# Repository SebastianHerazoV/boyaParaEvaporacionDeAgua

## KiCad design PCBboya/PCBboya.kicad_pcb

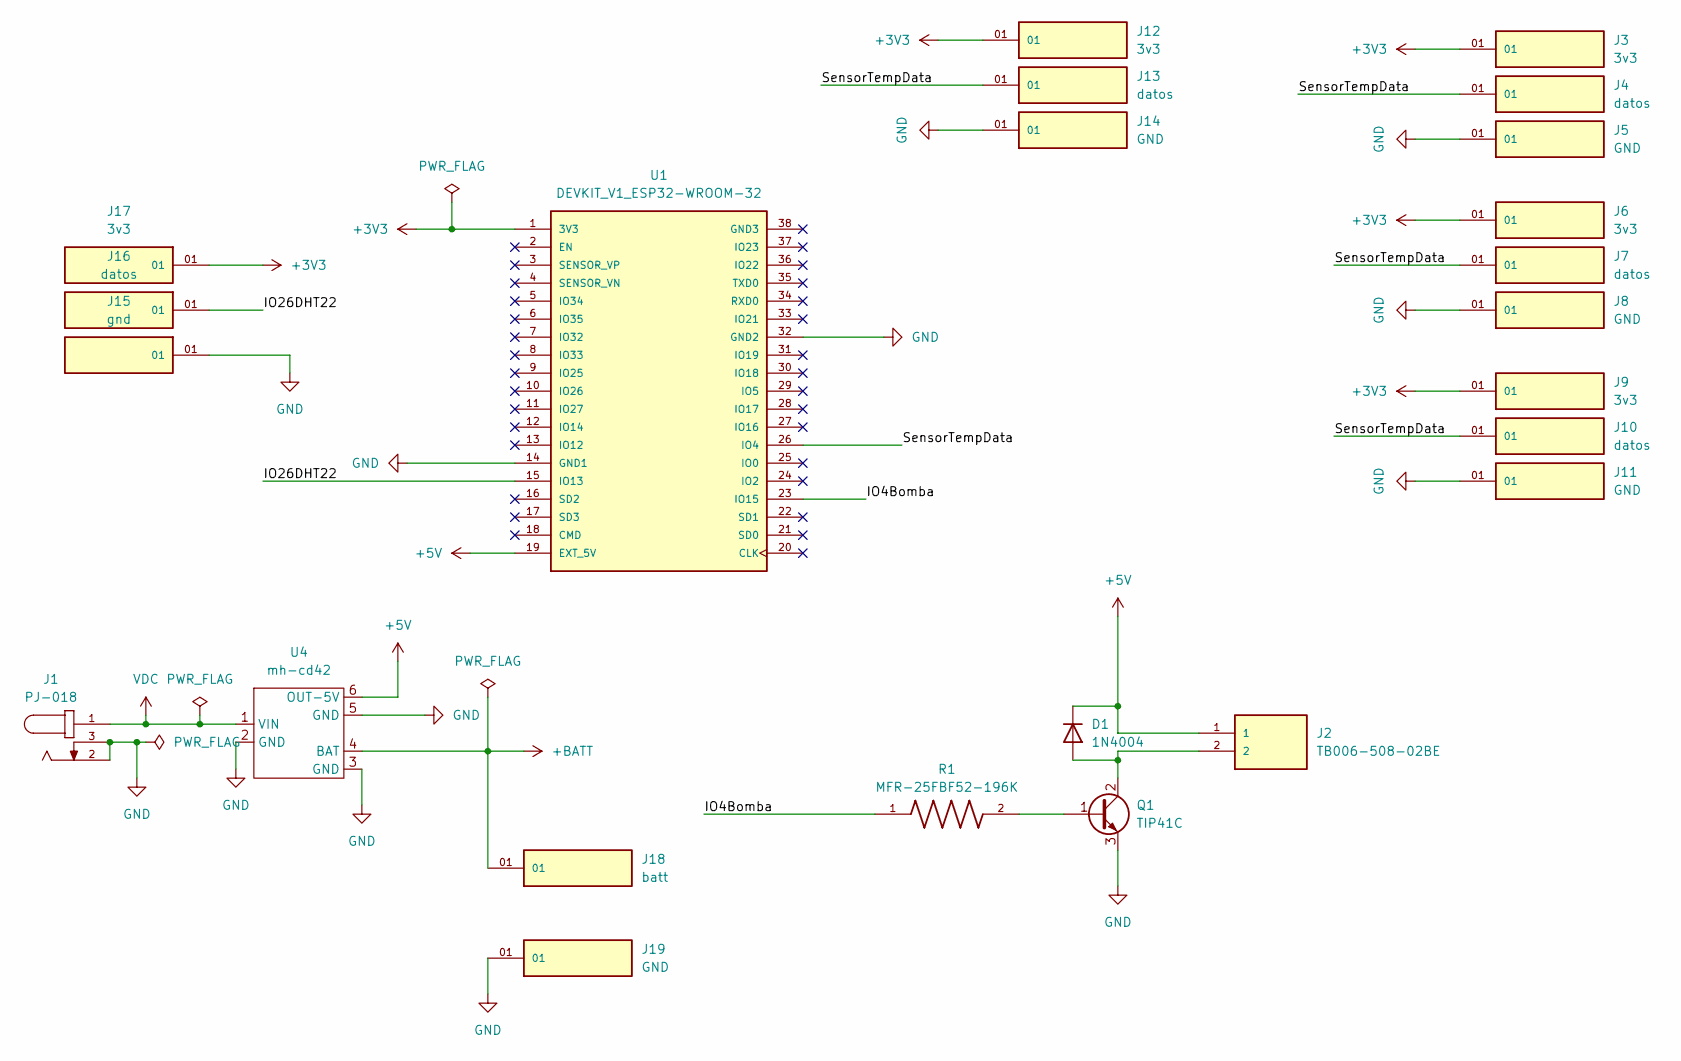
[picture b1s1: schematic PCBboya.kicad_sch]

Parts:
D1: 1N4004; D_DO-41_SOD81_P10.16mm_Horizontal
J1: PJ-018; CUI_PJ-002B
J2: TB006-508-02BE; CUI_TB006-508-02BE
J3, J6, J9, J12, J17: 3v3; SAMTEC_ESW-101-44-L-S; PARTREV R
J4, J7, J10, J13, J16: datos; SAMTEC_ESW-101-44-L-S; PARTREV R
J5, J8, J11, J14, J19: GND; SAMTEC_ESW-101-44-L-S; PARTREV R
J15: gnd; SAMTEC_ESW-101-44-L-S; PARTREV R
J18: batt; SAMTEC_ESW-101-44-L-S; PARTREV R
Q1: TIP41C; TO-220-3_Vertical
R1: MFR-25FBF52-196K; RESAD1100W55L680D260; PARTREV 201304
U1: DEVKIT_V1_ESP32-WROOM-32; MODULE_DEVKIT_V1_ESP32-WROOM-32; PARTREV N/A
U4: mh-cd42

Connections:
+3V3: J3.01, J6.01, J9.01, J12.01, J17.01, U1.1 (3V3)
+5V: D1.1 (K), J2.1, U1.19 (EXT_5V), U4.6 (OUT-5V)
+BATT: J18.01, U4.4 (BAT)
/IO4Bomba: R1.1, U1.23 (IO15)
/IO26DHT22: J16.01, U1.15 (IO13)
/SensorTempData: J4.01, J7.01, J10.01, J13.01, U1.26 (IO4)
GND: J1.2, J1.3, J5.01, J8.01, J11.01, J14.01, J15.01, J19.01, Q1.3 (E), U1.14 (GND1), U1.32 (GND2), U4.2 (GND), U4.3 (GND), U4.5 (GND)
unnamed: D1.2 (A), J2.2, Q1.2 (C)
unnamed: Q1.1 (B), R1.2
VDC: J1.1, U4.1 (VIN)

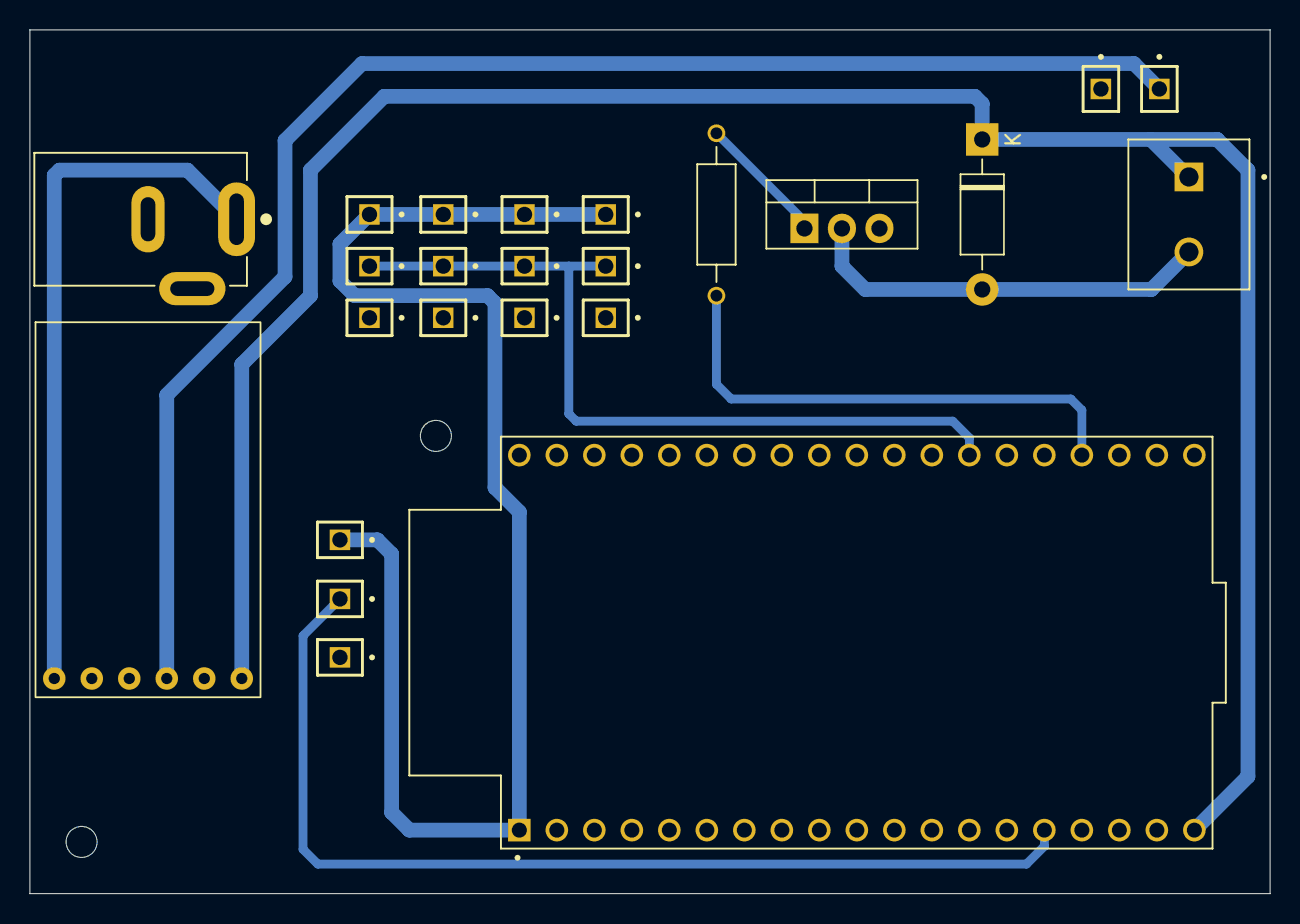
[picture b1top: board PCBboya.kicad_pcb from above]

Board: 2 copper layers, 84.0 x 58.5 mm, 24 parts (0 on the bottom side), 10 nets.
